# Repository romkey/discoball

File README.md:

# discoball ESP32 FastLED Board

*Use this hardware at your own risk. I am not responsible if it does not work for you, if you waste money on it, if it catches fire and burns down your home, if your hair falls out or if it causes an election to go sour. I promise no support; you are on your own.*

Discoball is a simple printed circuit board intended to run [vendo](https://github.com/romkey/vendo) FastLED-based software with a variety of types of RGB LEDs with built-in controllers, like the WS2812B or APA102. These LEDs usually need to be driven at 5V, so the board includes hardware to level shift the ESP32's 3.3v signals to 5V.

The discoball also includes an optional [BME280](https://www.bosch-sensortec.com/bst/products/all_products/bme280) or [BME680](https://www.bosch-sensortec.com/bst/products/all_products/bme680) air temperature/humidity/pressure and (on the 680) VOC sensor, and optional connections for external I2C devices.

Discoball is Open Source Hardware. This repo includes [schematic](eagle/discoball-v2.sch) and [board](eagle/discoball-v2.brd) files for Autodesk Eagle.

You can [order Disocball boards from OSHPark](https://oshpark.com/shared_projects/Rrn2Y8C1).

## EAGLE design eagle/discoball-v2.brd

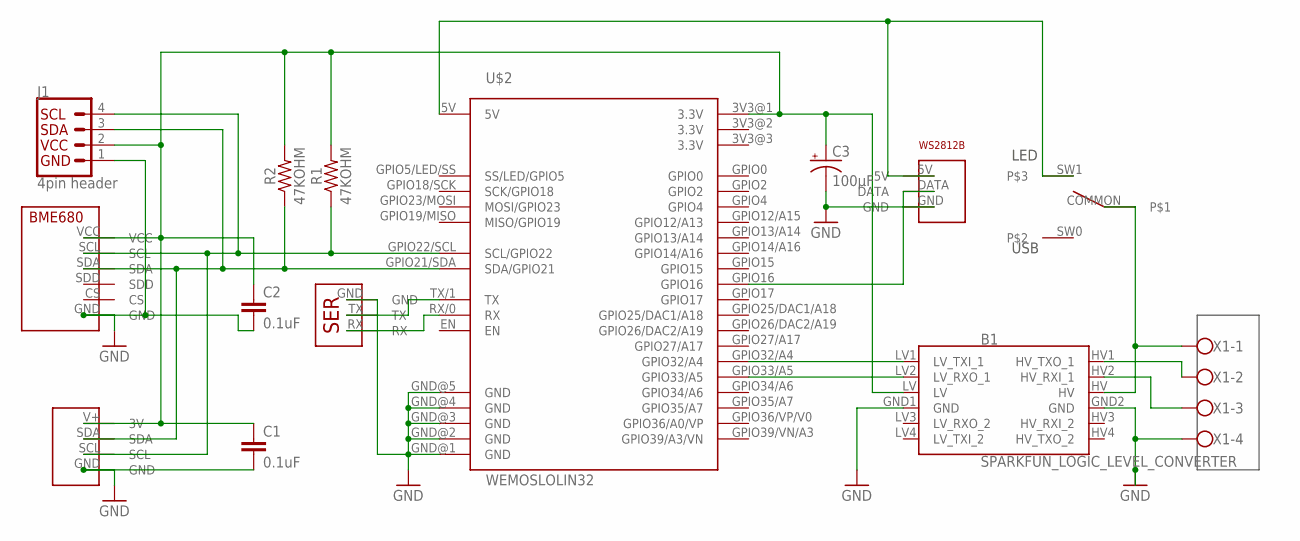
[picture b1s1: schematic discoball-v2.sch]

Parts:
B1: SPARKFUN_LOGIC_LEVEL_CONVERTER
C1, C2: 0.1uF; CAP-PTH-SMALL-KIT
C3: 100µF; CPOL-RADIAL-100UF-25V
J1: 4pin header; 1X04_1MM_RA
R1, R2: 47KOHM; AXIAL-0.3-KIT
U$1: BME680BREAKOUT
U$2: WEMOSLOLIN32; LOLIN32VAR1
U$3: I2CHEADER
U$4: SPDTSWITCH
U$6: SERIALHEADER
U$7: WS2812BHEADER
X1: W237-4

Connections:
3.3V: B1.LV, C1.1, C2.1, C3.1 (+), J1.2 (VCC), R1.P$2 (2), R2.P$2 (2), U$1.VCC, U$2.3V3@1 (3.3V), U$2.3V3@3 (3.3V), U$3.V+ (3V)
5V: U$2.5V, U$4.SW1, U$7.5V
GND: B1.GND1 (GND), B1.GND2 (GND), C1.2, C2.2, C3.2 (-), J1.1 (GND), U$1.GND, U$2.GND@1 (GND), U$2.GND@2 (GND), U$2.GND@3 (GND), U$2.GND@4 (GND), U$2.GND@5 (GND), U$3.GND, U$6.GND, U$7.GND, X1.4
unnamed: J1.4 (SCL), R1.P$1 (1), U$1.SCL, U$2.GPIO22/SCL (SCL/GPIO22), U$3.SCL
unnamed: J1.3 (SDA), R2.P$1 (1), U$1.SDA, U$2.GPIO21/SDA (SDA/GPIO21), U$3.SDA
unnamed: B1.HV2 (HV_RXI_1), X1.3
unnamed: U$2.RX/0 (RX), U$6.RX
unnamed: B1.LV1 (LV_TXI_1), U$2.GPIO32/A4
unnamed: B1.LV2 (LV_RXO_1), U$2.GPIO33/A5
unnamed: U$2.TX/1 (TX), U$6.TX
unnamed: B1.HV1 (HV_TXO_1), X1.2
unnamed: B1.HV, U$4.COMMON, X1.1
unnamed: U$2.GPIO16, U$7.DATA

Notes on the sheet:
LED
USB

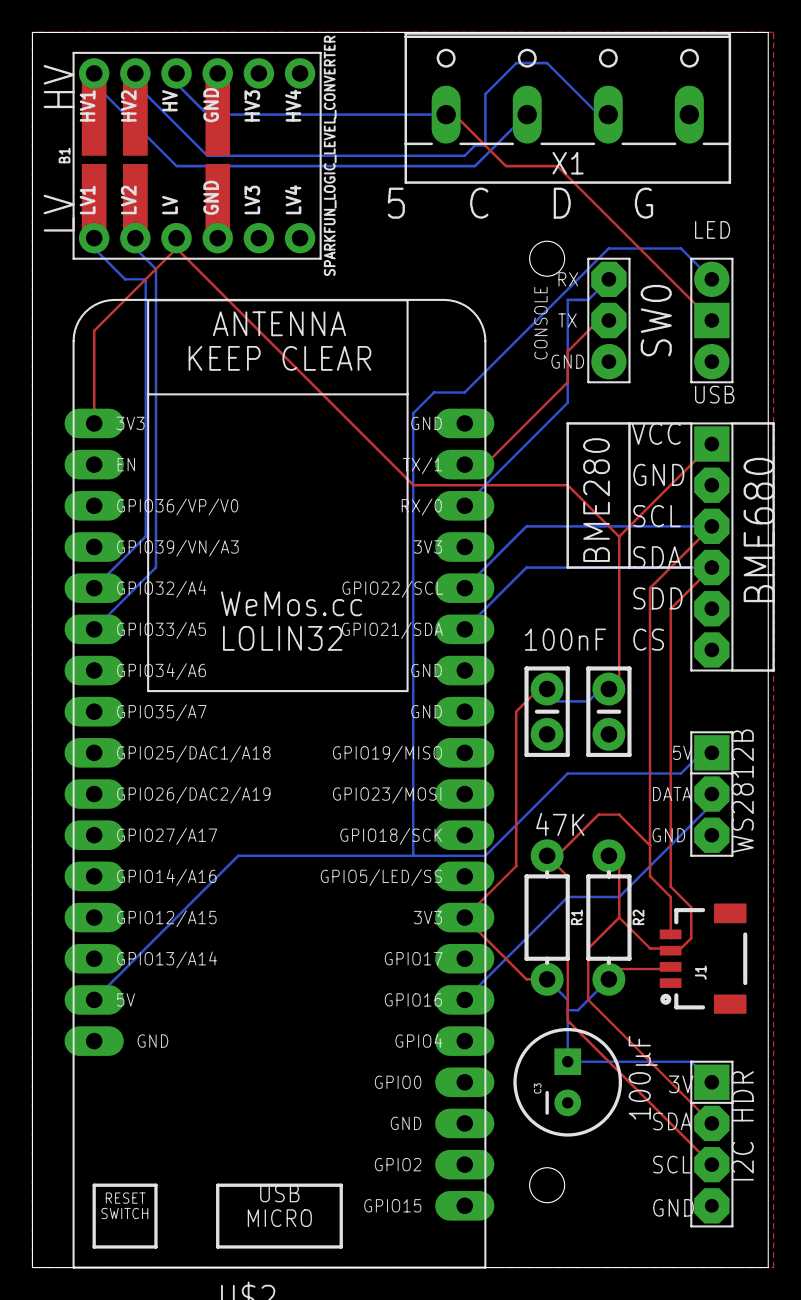
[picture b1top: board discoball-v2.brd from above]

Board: 2 copper layers, 45.4 x 76.2 mm, 15 parts (1 on the bottom side), 13 nets.

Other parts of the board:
U$5: OSHW-LOGO-L

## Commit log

2019-10-31 get some documentation in there
2019-10-31 updated parts
2019-10-31 updated front photo
2019-10-31 minor README updates
2019-10-31 links
2019-10-31 schematic is .png
2019-10-31 I2C support
2019-10-31 emphasis

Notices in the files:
parts and their libraries:
SparkFun-Capacitors: Licensing: Creative Commons ShareAlike 4.0 International - https://creativecommons.org/licenses/by-sa/4.0
